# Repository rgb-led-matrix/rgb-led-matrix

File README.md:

# rgb-led-matrix
This repository creates a library for top level applications and graphics. This repository will be a sub-module to that repository. The purpose of this code base is to allow better support for different small form factor boards regardless of hardware, operating system, etc. It also allows for support of different implementations.

Only external implementations are used. These should enable better performance and portability, despite possibly being more expensive.

## Status
Work in progress. 

## License
Code is licensed under GPL 3. The original code base was https://github.com/hzeller/rpi-rgb-led-matrix. This code base has diverged from the original code base signifcantly. (I went another direction with it.) Original was GPL 2. (For original terms see git history or upstream.)

There is no warranty for this. Work is free to use according to the [GPL 3 license](LICENSE). I am not responsible or liable for any damages or issues as a result of this in any way. User is responsible for all laws and regulations as required. Work is AS-IS and it is the respiblity of any user to address any shortages discovered in this code base before using it.

## Building
Note this is a hack for now. Currently it builds both the Raspberry Pi and Rock Pi S.

```bash
bash build.sh
```

## Layout
There are three sections at this directory level. Look at lower levels for more details about each section.

### external
This is a section for hardware offload modules used in rgb-led-matrix/lib/src/framebuffer. Some external modules may have better features.

### rgb-led-matrix
This is the main library source directory. The top level library includes are in rgb-led-matrix/include while the internal source is divided into rgb-led-matrix/lib which has an include and src folder. Applications do not need to worry about the internal logic, just the top level includes and the libraries.

### scripts
This is a folder containing helper scripts for setup and other things. These will be referenced by other sections.

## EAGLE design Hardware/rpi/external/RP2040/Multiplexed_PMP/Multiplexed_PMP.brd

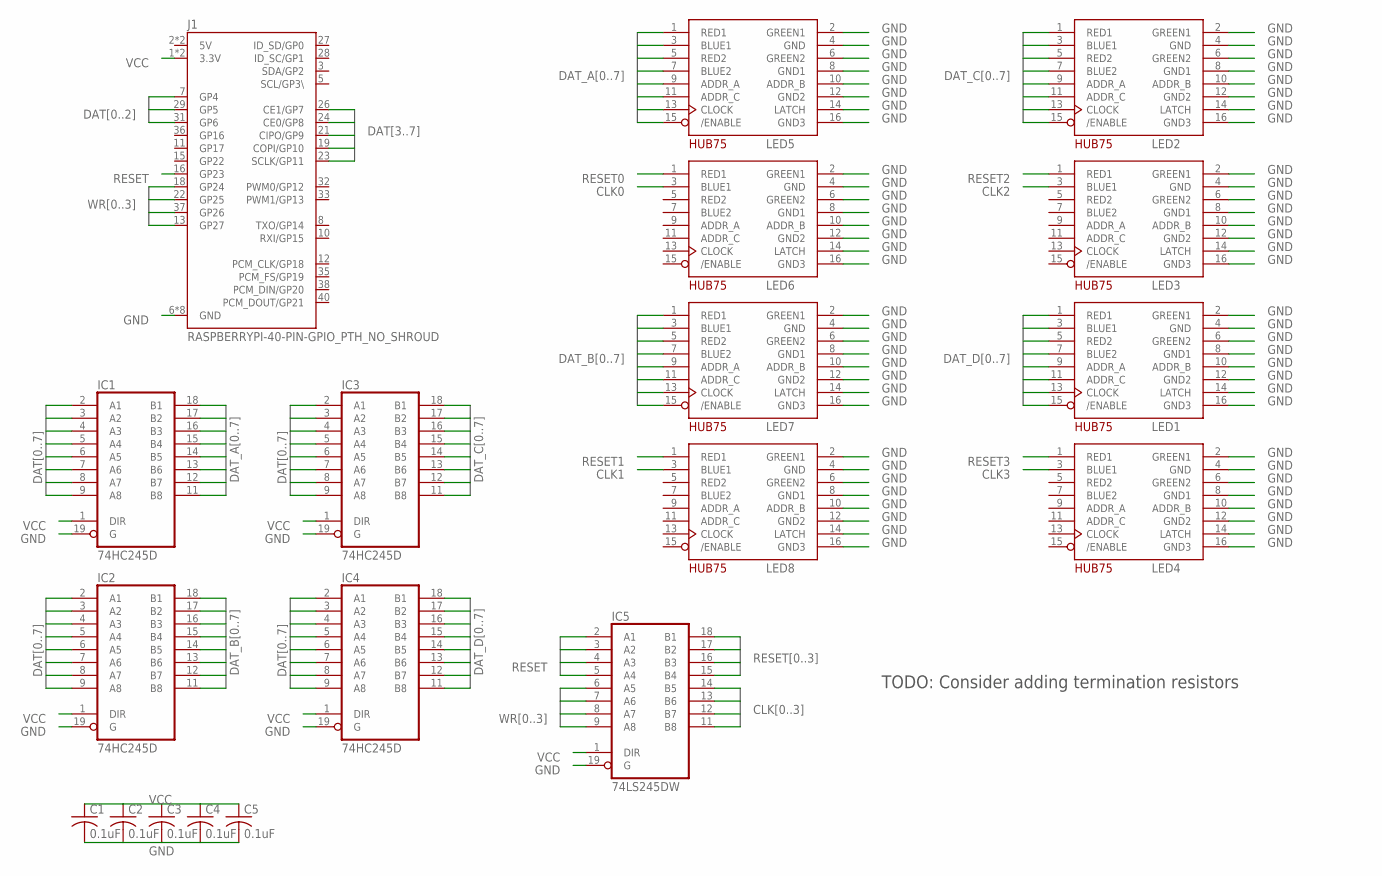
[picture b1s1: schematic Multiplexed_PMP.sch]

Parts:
C1, C2, C3, C4, C5: 0.1uF; C0805
IC1, IC2, IC3, IC4: 74HC245D; SO20W
IC5: 74LS245DW; SO20W
J1: RASPBERRYPI-40-PIN-GPIO_PTH_NO_SHROUD; 2X20
LED1, LED2, LED3, LED4, LED5, LED6, LED7, LED8: HUB75MATRIX; 2X08-IDC

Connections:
5V: J1.2 (5V), J1.4 (5V)
CLK0: IC5.14 (B5), LED6.3 (BLUE1)
CLK1: IC5.13 (B6), LED8.3 (BLUE1)
CLK2: IC5.12 (B7), LED3.3 (BLUE1)
CLK3: IC5.11 (B8), LED4.3 (BLUE1)
DAT0: IC1.2 (A1), IC2.2 (A1), IC3.2 (A1), IC4.2 (A1), J1.7 (GP4)
DAT1: IC1.3 (A2), IC2.3 (A2), IC3.3 (A2), IC4.3 (A2), J1.29 (GP5)
DAT2: IC1.4 (A3), IC2.4 (A3), IC3.4 (A3), IC4.4 (A3), J1.31 (GP6)
DAT3: IC1.5 (A4), IC2.5 (A4), IC3.5 (A4), IC4.5 (A4), J1.26 (CE1/GP7)
DAT4: IC1.6 (A5), IC2.6 (A5), IC3.6 (A5), IC4.6 (A5), J1.24 (CE0/GP8)
DAT5: IC1.7 (A6), IC2.7 (A6), IC3.7 (A6), IC4.7 (A6), J1.21 (CIPO/GP9)
DAT6: IC1.8 (A7), IC2.8 (A7), IC3.8 (A7), IC4.8 (A7), J1.19 (COPI/GP10)
DAT7: IC1.9 (A8), IC2.9 (A8), IC3.9 (A8), IC4.9 (A8), J1.23 (SCLK/GP11)
DAT_A0: IC1.18 (B1), LED5.1 (RED1)
DAT_A1: IC1.17 (B2), LED5.3 (BLUE1)
DAT_A2: IC1.16 (B3), LED5.5 (RED2)
DAT_A3: IC1.15 (B4), LED5.7 (BLUE2)
DAT_A4: IC1.14 (B5), LED5.9 (ADDR_A)
DAT_A5: IC1.13 (B6), LED5.11 (ADDR_C)
DAT_A6: IC1.12 (B7), LED5.13 (CLOCK)
DAT_A7: IC1.11 (B8), LED5.15 (/ENABLE)
DAT_B0: IC2.18 (B1), LED7.1 (RED1)
DAT_B1: IC2.17 (B2), LED7.3 (BLUE1)
DAT_B2: IC2.16 (B3), LED7.5 (RED2)
DAT_B3: IC2.15 (B4), LED7.7 (BLUE2)
DAT_B4: IC2.14 (B5), LED7.9 (ADDR_A)
DAT_B5: IC2.13 (B6), LED7.11 (ADDR_C)
DAT_B6: IC2.12 (B7), LED7.13 (CLOCK)
DAT_B7: IC2.11 (B8), LED7.15 (/ENABLE)
DAT_C0: IC3.18 (B1), LED2.1 (RED1)
DAT_C1: IC3.17 (B2), LED2.3 (BLUE1)
DAT_C2: IC3.16 (B3), LED2.5 (RED2)
DAT_C3: IC3.15 (B4), LED2.7 (BLUE2)
DAT_C4: IC3.14 (B5), LED2.9 (ADDR_A)
DAT_C5: IC3.13 (B6), LED2.11 (ADDR_C)
DAT_C6: IC3.12 (B7), LED2.13 (CLOCK)
DAT_C7: IC3.11 (B8), LED2.15 (/ENABLE)
DAT_D0: IC4.18 (B1), LED1.1 (RED1)
DAT_D1: IC4.17 (B2), LED1.3 (BLUE1)
DAT_D2: IC4.16 (B3), LED1.5 (RED2)
DAT_D3: IC4.15 (B4), LED1.7 (BLUE2)
DAT_D4: IC4.14 (B5), LED1.9 (ADDR_A)
DAT_D5: IC4.13 (B6), LED1.11 (ADDR_C)
DAT_D6: IC4.12 (B7), LED1.13 (CLOCK)
DAT_D7: IC4.11 (B8), LED1.15 (/ENABLE)
GND: C1.2, C2.2, C3.2, C4.2, C5.2, IC1.10 (GND), IC1.19 (G), IC2.10 (GND), IC2.19 (G), IC3.10 (GND), IC3.19 (G), IC4.10 (GND), IC4.19 (G), IC5.10 (GND), IC5.19 (G), J1.6 (GND), J1.9 (GND), J1.14 (GND), J1.20 (GND), J1.25 (GND), J1.30 (GND), J1.34 (GND), J1.39 (GND), LED1.2 (GREEN1), LED1.4 (GND), LED1.6 (GREEN2), LED1.8 (GND1), LED1.10 (ADDR_B), LED1.12 (GND2), LED1.14 (LATCH), LED1.16 (GND3), LED2.2 (GREEN1), LED2.4 (GND), LED2.6 (GREEN2), LED2.8 (GND1), LED2.10 (ADDR_B), LED2.12 (GND2), LED2.14 (LATCH), LED2.16 (GND3), LED3.2 (GREEN1), LED3.4 (GND), LED3.6 (GREEN2), LED3.8 (GND1), LED3.10 (ADDR_B), LED3.12 (GND2), LED3.14 (LATCH), LED3.16 (GND3), LED4.2 (GREEN1), LED4.4 (GND), LED4.6 (GREEN2), LED4.8 (GND1), LED4.10 (ADDR_B), LED4.12 (GND2), LED4.14 (LATCH), LED4.16 (GND3), LED5.2 (GREEN1), LED5.4 (GND), LED5.6 (GREEN2), LED5.8 (GND1), LED5.10 (ADDR_B), LED5.12 (GND2), LED5.14 (LATCH), LED5.16 (GND3), LED6.2 (GREEN1), LED6.4 (GND), LED6.6 (GREEN2), LED6.8 (GND1), LED6.10 (ADDR_B), LED6.12 (GND2), LED6.14 (LATCH), LED6.16 (GND3), LED7.2 (GREEN1), LED7.4 (GND), LED7.6 (GREEN2), LED7.8 (GND1), LED7.10 (ADDR_B), LED7.12 (GND2), LED7.14 (LATCH), LED7.16 (GND3), LED8.2 (GREEN1), LED8.4 (GND), LED8.6 (GREEN2), LED8.8 (GND1), LED8.10 (ADDR_B), LED8.12 (GND2), LED8.14 (LATCH), LED8.16 (GND3)
RESET: IC5.2 (A1), IC5.3 (A2), IC5.4 (A3), IC5.5 (A4), J1.16 (GP23)
RESET0: IC5.18 (B1), LED6.1 (RED1)
RESET1: IC5.17 (B2), LED8.1 (RED1)
RESET2: IC5.16 (B3), LED3.1 (RED1)
RESET3: IC5.15 (B4), LED4.1 (RED1)
VCC: C1.1, C2.1, C3.1, C4.1, C5.1, IC1.1 (DIR), IC1.20 (VCC), IC2.1 (DIR), IC2.20 (VCC), IC3.1 (DIR), IC3.20 (VCC), IC4.1 (DIR), IC4.20 (VCC), IC5.1 (DIR), IC5.20 (VCC), J1.1 (3.3V), J1.17 (3.3V)
WR0: IC5.6 (A5), J1.18 (GP24)
WR1: IC5.7 (A6), J1.22 (GP25)
WR2: IC5.8 (A7), J1.37 (GP26)
WR3: IC5.9 (A8), J1.13 (GP27)

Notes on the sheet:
TODO: Consider adding termination resistors

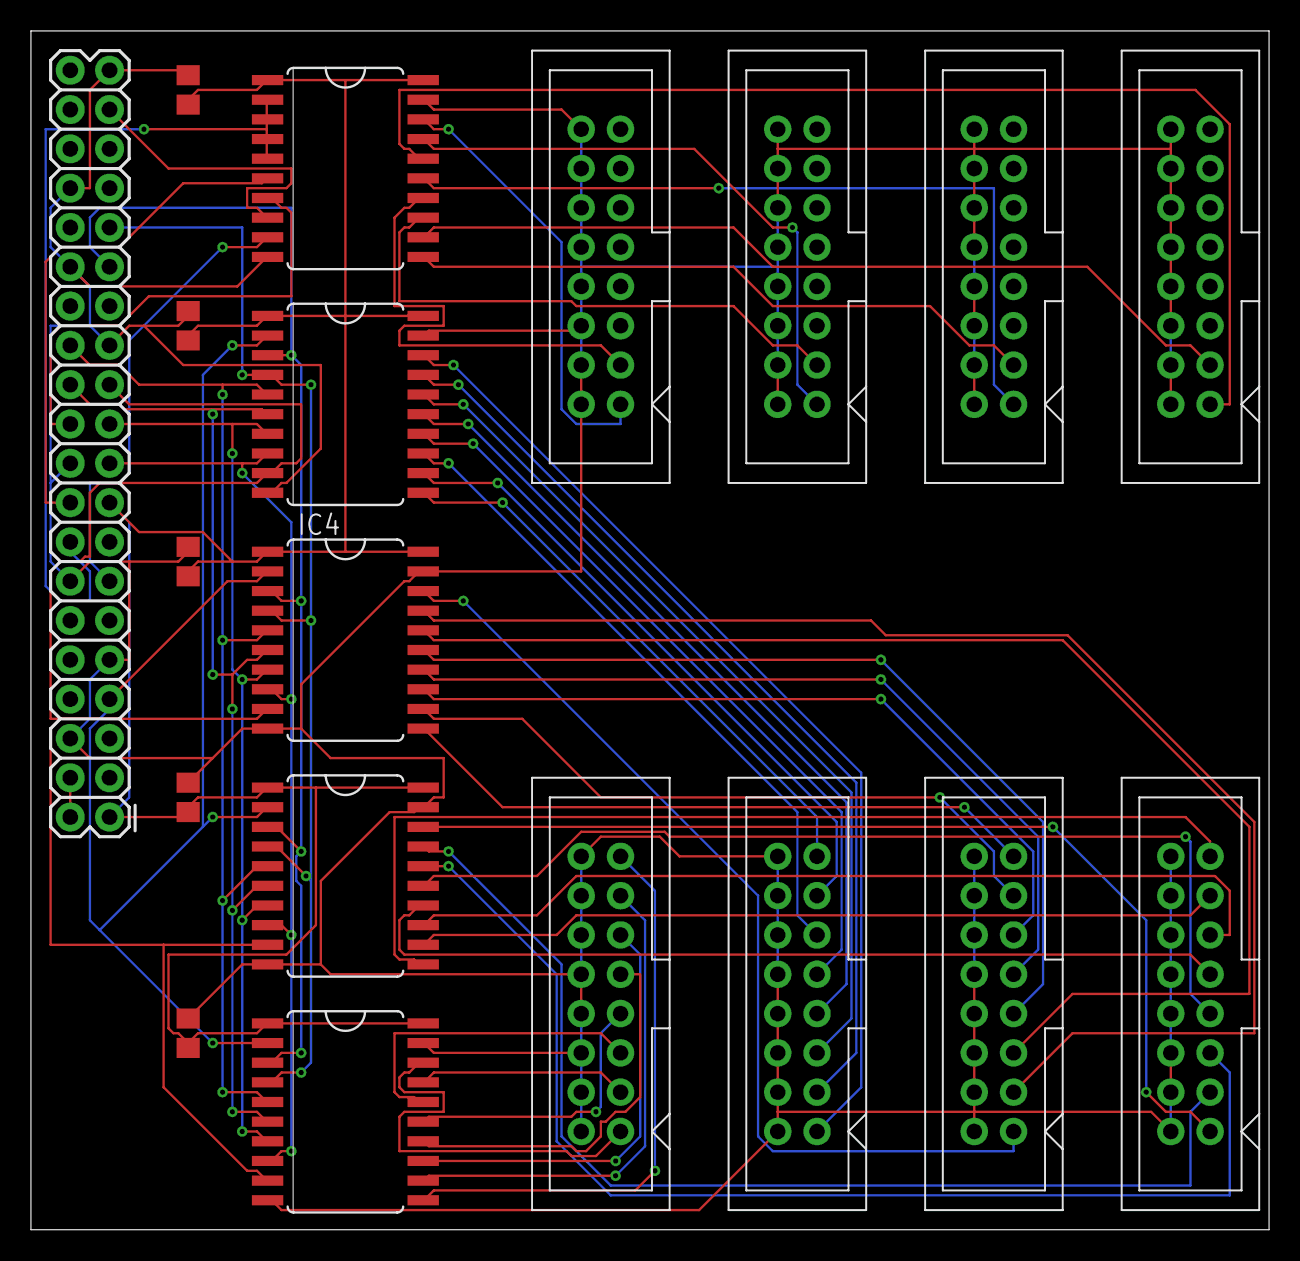
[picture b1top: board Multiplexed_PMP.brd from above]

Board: 2 copper layers, 80.0 x 77.5 mm, 19 parts (0 on the bottom side), 56 nets.

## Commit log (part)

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2023-06-07 #55 Updates
2023-06-08 Adding FTDI D2XX libraries
2023-06-08 Fixing FTDI D2XX libraries
2023-06-08 Updating documentation for build logic
2023-06-09 Changing back to RP2040_UART to support serial_uart protocol of RP2040
2023-06-09 Cleaning up IO stuff
2023-06-09 add linux 64-bit
2023-06-16 Updating FTDI logic
2023-08-23 Removing CIE1931. May add interface color mapper to Framebuffer or CFG at some point. CIE1931 may not be correct for red, green and/or blue. CIE1931 may not be correct for every LED either.
2023-08-29 Create LICENSE
2023-09-12 Removing mutex from framebuffer. This is done to support PIC32, Cortex-M7 (Teensy 4), etc. Application logic which works with Panel and Panel Pixel Mapper must serialize calls to show and set pixel. 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
2023-09-13 #72 Checking to make IO Nodes are not duplicated in MultiPanel_Mapper. Aka cannot put multiple buffers(Panel and Panel_Pixel_Mapper) into the same Frame (MultiPanel_Mapper)
2023-09-14 #72 Updates
2023-09-14 Removing external RP2040 Framebuffer. Was considering keeping it but decided against it.
2023-09-14 We have a circular dependency chain forming.
2024-01-22 Removing FTDI out of concerns for real time performance of USB.
2024-02-14 Fix merge conflict
2024-02-14 #79 Add exceptions
2024-02-14 Delete external/RP2040/cfg.xml
    Not used anymore
2024-02-14 Add scheduler back. Did not upgrade. Will remove threading at some point or make thread safe.
2024-02-14 Work in progress
2024-02-15 adding doxygen config
2024-02-15 Clean up
2024-02-15 Adding exceptions
2024-02-15 Adding frame manager
2024-02-16 Trying to break up panel interface to be more pure. Still working on intensity mapper, but running into conflict with Framebuffer templating. Could move that around but not sure if this will work lon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
2024-02-16 fixing multipanel by calling internal factory
2024-02-16 add locks
2024-02-16 fix typo
2024-02-16 Break up Event into Single_Panel and MultiPanel. Drop Protocol from CFG. Combine Single_Panel and MultiPanel into Frame. Replace Event with Frame. Replace all notions of Panel with MultiPanel or Sing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
2024-02-16 Nope diamond...still there in the same placegit push!
2024-02-16 I have wasted so much time on this. Just call show from the Pixel implementation. I am protected by the constructor for show. I fixed MultiPanel in theory...
2024-02-17 Removing multiplex mapper (Panel Type) from CFG. This belongs in Pixel Mapper instead.
2024-02-17 Moving scheduler to internal
2024-02-17 Hidding implementation of MultiPanel
2024-02-17 Remove Panel interface
2024-02-17 Fix issue in scheduler for multipanel
2024-02-17 Starting Frame Manager
2024-02-18 Add ability to reduce thread count
2024-02-18 Make Scheduler threadless. Show is now blocking. This will make show in Single_Panel and MultiPanel blocking. Frame_Manager however is threaded.
2024-02-18 Clean up scheduler. Add double buffering to test. Pass show through pixel mapper interface.
2024-02-18 Removing Root
2024-02-18 Adding quick loop logic for multipanel... May want to consider optimization at some point.
2024-02-18 Parameter checks
2024-02-18 Test header
2024-02-18 Adding locks
2024-02-19 Add Direction to MultiPanel. Add some threading to MultiPanel_Internal for SMP style acceleration. Finished Outdoor Pixel Mapper.
2024-02-19 Breaking up Pixel and Multiplex Mapper
2024-02-19 Restricting resize to just Panel_Internal
2024-02-19 Work in progress thread pool
2024-02-19 Make thread pool life forever
2024-02-21 Adding comment. Note I will likely need to refactor Multiplex and Pixel.
2024-02-21 Adding ability to create packets in protocol
2024-02-21 Prevent deadlock. Will need to revisit this.
2024-02-21 Attempt to release locks on errors. Need to add try-catch blocks in code to complete this. Need to come back to this.
2024-03-09 Add logger
2024-03-09 Adding comment
2024-03-13 Update Frame_Manager.cpp
    Add warning about using async frame manager
2024-03-21 removing multipanel to avoid glitches
2024-03-29 Revert "Merge pull request #5 from daveythacher/updates"
    This reverts commit 5c77525a1513c283e7b6c6fb431b39ff81a227d9, reversing
    changes made to c3a0d26b94a5277af1fba33dc422547d4aca7c5e.
2024-03-29 Adding control node
2024-05-04 Adding random app note about random experiment which is not really useful at the moment. May be of value in the future or not. Note I have decided to move away from loafer system due to IO complexity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
2024-05-04 This needs work. Planning to merge thread pools and create priority.
2024-05-04 Revert "This needs work. Planning to merge thread pools and create priority." This is crazy, so backing it out.
    This reverts commit 72611612bda6cd7d98da36b3ce8492f83a32c411.
2024-05-05 Remove templates in threadpool
2024-05-07 Fix conflict in threadpool
2024-05-07 Fix stuck in error...error
2024-05-08 Attempt to block multi-submission of send in protocol.
2024-05-13 Fix state machine in RP2040 protocol
2024-05-13 #98 Some magic number stuff for custom header/delimiter
2024-05-13 #98 updates
2024-05-13 Hiding internals
2024-05-13 Forgot this..
2024-05-13 Merging Control into Protocol. Work in progress. Multi-Panel is once again problematic with control node as no current checks exist.
2024-05-14 #98 hack protocol issue for now
2024-05-14 Updates:
2024-05-16 Moving stuff around
2024-05-19 some exception and logging logic
2024-05-24 Remove subclasses
2024-05-30 adding incomplete test node. This should help decouple testing from IO, however timing will be hard to model with this. We should not need this by design any how.
2024-06-20 Add exceptions
2024-07-18 This should have been in the first draft
2024-11-13 Removing last friend
2024-11-13 updating includes to use correct format

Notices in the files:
parts and their libraries:
SparkFun-Connectors: Licensing: Creative Commons ShareAlike 4.0 International - https://creativecommons.org/licenses/by-sa/4.0
